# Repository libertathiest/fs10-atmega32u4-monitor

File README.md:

# FS10 Standalone Monitor (ATmega32U4)

A standalone USB monitor and configuration tool for the FCI FS10 Flow Switch, built around the **ATmega32U4** on an Arduino Leonardo–compatible board. It talks to the FS10 over a UART passthrough and shows flow switch condition both graphically and as text on an onboard TFT display — an independent, personal-project replacement for the legacy (uncertified) FCI power accessory.

This was designed, laid out, and manufactured end-to-end: schematic capture and PCB layout in KiCad, enclosure design in FreeCAD, and production through JLCPCB. Physical units are built and in active use.

## Hardware

- **MCU:** ATmega32U4 (Arduino Leonardo form factor, 68.6×53.4mm outline)
- **Display:** 2.4" 240×320 SPI TFT, ILI9341 driver (Adafruit_GFX + Adafruit_ILI9341)
- **Power:** UART passthrough with power arbitration between USB and an external 24V supply; ships with a UL/ETL/CE/FCC-certified wall adapter
- **Enclosure:** Hammond 1593-series compatible, modeled in FreeCAD (STL + parametric source included)
- **PCB:** Designed in KiCad (originally imported from EasyEDA Pro); manufactured and assembled via JLCPCB

## Repo layout

```
firmware/   Arduino sketch (.ino) — display driver, UART passthrough, UI
hardware/   KiCad project (schematic/PCB), FreeCAD enclosure, JLCPCB gerbers + BOM
Assets/     Schematic PDF, design docs, product flyer, front label preview
notes/      Supporting reference material
```

## Status

Completed. Units are built, deployed, and in day-to-day field use.

---
*This is an independently developed project, not an official FCI-branded product.*

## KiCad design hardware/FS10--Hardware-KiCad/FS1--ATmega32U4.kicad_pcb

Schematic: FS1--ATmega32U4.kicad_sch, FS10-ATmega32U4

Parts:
BZ1: Buzzer_5V; MagneticBuzzer_ProSignal_ABT-410-RC; Mfg Part # ABT-410-RC; JLCPCB C252917
C1, C2, C11: 100nF; C_0603_1608Metric; Manufacturer Part CC0603KRX7R9BB104; JLCPCB C14663
C4: 10uF 50V; C_1210_3225Metric; Manufacturer Part CC1210KKX7R9BB106; JLCPCB C596319
C8, C9, C16, C21: 100nF; C_0603_1608Metric; Manufacturer Part CC0603KRX7R9BB104; Digikey_ref 399-C0603C104J4RAC7867CT-ND
C10, C25, C26: 22uF; C_1206; Voltage Rated 10V; Tolerance ±10%; Part CL31A226KPHNNNE; LCSC C5672
C13, C19: 1uF; C_0603_1608Metric; Manufacturer Part CL10A105KB8NNNC; Digikey_ref 399-C0603C105K4RAC7411CT-ND
C14, C15, C17, C18: 1uF; C_0603_1608Metric; Manufacturer Part CL10A105KB8NNNC; JLCPCB C15849
C20: 10u; CP_EIA-3528-21_Kemet-B; Manufacturer Part CA45A-B-20V-10UF-K; Digikey_ref 399-3708-1-ND
C22, C23: 22pF; C_0603; Voltage Rated 50V; Tolerance ±5%; Part CL10C220JB8NNNC; LCSC C1653
C24: 100pF; C_0603; Voltage Rated 50V; Tolerance ±5%; Part CL10C101JB8NNNC; LCSC C14858
CN1: M12_8POS_PIGTAIL_TERMINATION; SIP-9_P2.54mm_Oval; not fitted
D1: SS34B; D_SMB; Manufacturer Part SS34B; LCSC Part Name 3A 40V SMB Schottky diode for buck 5V i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
D2: SMBJ28A-TR; D_SMB; Manufacturer Part SMBJ28A-TR; LCSC Part Name 28V standoff, 45.4V clamp, 600W unidire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
D3: 1N4148W-TP; D_SOD-123; Manufacturer Part 1N4148W-TP; Digikey_ref 1N4148WTPMSCT-ND
D4: SP0503BAHTG; SOT-143; Manufacturer Part SP0503BAHTG; JLCPCB C3040626
D5: US1A; D_SMA; Forward Voltage (Vf@If) 1V@1A; Reverse Voltage (Vr) 50V; Manufacturer Part US1A; LCSC Part Name 1V@1A 50ns Independent Type 1A 50V SMA(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
D6: SS14; D_SMA; Manufacturer Part SS14; LCSC Part Name USB VBUS Schottky isolation into +5V sy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
F1: MF-MSMF050-2; Fuse_1812_4532Metric; Manufacturer Part MF-MSMF050-2; LCSC Part Name 500mA 15V 1812 resettable PTC fuse
H1, H2, H3, H4: M3_SELF_TAP_HOLE; MountingHole_3.2mm_M3
IC2: AP63200WU-7; TSOT-23-6; Manufacturer Part AP63200WU-7; LCSC Part Name 3.8V-32V input, adjustable 2A synchrono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
ICSP1: ICSP; PinHeader_2x03_P2.54mm_Vertical; Digikey_ref A128860-ND; not fitted
J1: DC005; BarrelJack_GCT_DCJ200-10-A_Horizontal; Manufacturer Part DC005; LCSC Part Name DC barrel jack, switched, through-hole,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
J11: Encoder module; PinHeader_1x05_P2.54mm_Vertical
J12: ILI9341 Display; PinHeader_1x10_P2.54mm_Vertical
J13: OLED_I2C_OPTION; PinHeader_1x04_P2.54mm_Vertical; not fitted
L1: 10uH; L_Sunlord_SWPA5040S; Manufacturer Part CKCS5040-10uH/M; JLCPCB C354610
L2: MH2029-300Y; L_0805_2012Metric; Manufacturer Part MH2029-300Y; Digikey_ref MH2029-300YCT-ND
LED1: Wurth_WL-SFTW; LED_RGB_Wuerth-PLCC4_3.2x2.8mm_150141M173100
LED2: 5mm led hand-soldered; LED_D5.0mm-4_RGB
Q_BZ1: 2N7002; SOT-23; LCSC Part Name Low-side MOSFET driver for 5V magnetic 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
R1, R14, R15: 1kΩ; R_0603; Overload Voltage (Max) 75V; Tolerance ±1%; Manufacturer Part 0603WAF1001T5E; LCSC Part Name 100mW Thick Film Resistors 75V ±100ppm/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
R2: 100K; R_0603_1608Metric; Manufacturer Part 0603WAF1003T5E; LCSC Part Name Resistance:100kΩ Package:0603 ±1% 100mW
R3, R4: 1M; R_0603_1608Metric; Manufacturer Part 0603WAF1004T5E; LCSC Part Name Resistance:1MΩ Package:0603 ±1% 100mW
R5, R6: 22; R_0603_1608Metric; Manufacturer Part 0603WAF220JT5E; LCSC Part Name Resistance:22Ω Package:0603 ±1% 100mW
R7: 150k; R_0603_1608Metric; Manufacturer Part 0603WAF1503T5E; LCSC Part Name Resistance:150kΩ Package:0603 ±1% 100mW
R8: 22k; R_0603_1608Metric; Manufacturer Part 0603WAF2202T5E; LCSC Part Name Resistance:22kΩ Package:0603 ±1% 100mW
R9: 169K; R_0603_1608Metric; Manufacturer Part 0603WAF1693T5E; LCSC Part Name Resistance:169kΩ Package:0603 ±1% 100mW
R10: 30K; R_0603_1608Metric; Manufacturer Part 0603WAF3002T5E; LCSC Part Name Resistance:30kΩ Package:0603 ±1% 100mW
R21: 270Ω; R_0805; Overload Voltage (Max) 150V; Tolerance ±1%; Manufacturer Part 0805W8F2700T5E; LCSC Part Name 125mW Thick Film Resistors 150V ±100ppm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
RESET1: SKHHLUA010; SW_Tactile_SKHH_Angled; Manufacturer Part SKHHLUA010; LCSC C139764
R_BZ1: 1k; R_0805_2012Metric; Manufacturer Part 0805W8F1001T5E; LCSC Part Name Resistance:1kΩ Package:0805 ±1% 125mW
R_BZ2: 100k; R_0805_2012Metric; Manufacturer Part 0805W8F1003T5E; LCSC Part Name Resistance:100kΩ Package:0805 ±1% 125mW
SW1: HX KCD11-BL; SW-TH_KCD11-BL; Manufacturer Part HX KCD11-BL; JLCPCB C6917329
SW2: K2-1102SP-A4SC-04; Push_Hybrid_SMD_THR_12x12mm; Manufacturer Part K2-1102SP-A4SC-04; LCSC Part Name 12x12mm SMD-4P SPST tactile switch, 7.5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
TP1, TP2: Pin_D0.9mm_L10.0mm_W2.4mm_FlatFork
TP4, TP5, TP6, TP7: TP; SolderWire-0.1sqmm_1x01_D0.4mm_OD1mm
U2: ATMEGA32U4-XUAU; TQFP-44_10x10mm_P0.8mm; Manufacturer Part ATMEGA32U4-AU; JLCPCB C44854
U3: MAX232EIDR; SOIC-16_3.9x9.9mm_P1.27mm; Manufacturer Part MAX232EIDR; JLCPCB C273639
USB1: USB-109C-B-CU; USB-B-TH_USB-109C-B-CU; Manufacturer Part USB-109C-B-CU; JLCPCB C20611692
X1: X322516MLB4SI; OSC-SMD_4P-L3.2-W2.5-BL; Frequency Tolerance ±10ppm; Manufacturer Part X322516MLB4SI; LCSC Part Name 16MHz Surface Mount Crystal 9pF ±10ppm 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

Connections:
24V: C1.1, C4.1 (+), CN1.1 (WTE), IC2.2 (EN), IC2.3 (VIN), R7.1, SW1.2
+4-20: CN1.3 (GRN), TP1.1 (1_1)
+5V: C11.2, D1.1 (C), D6.1 (C), ICSP1.2, J11.2, J12.1 (+5V), J12.8 (LED+), J12.10 (TFT_BL), J13.2, L2.2, LED1.1 (A), LED2.2 (A), R21.1, U2.2 (UVCC), U2.14 (VCC), U2.34 (VCC1), U3.16 (VCC)
/24Vraw: D2.1 (C), J1.1, SW1.1
/AREF: C13.2, C16.2, U2.42 (AREF)
/AVCC: C8.1, C9.1, D3.1 (C), L2.1, U2.24 (AVCC), U2.44 (AVCC1)
/BLU: CN1.7 (BLU), U3.14 (DOUT1)
/BUCK_RAW: C10.1, C24.1, C25.1, C26.1, D1.2 (A), L1.2, R9.2
/BUZZER_CTRL: R_BZ1.1, U2.29 ((PCINT5/OC1A/#OC4B/ADC12)PB5)
/ENC_A_D4: J11.5, U2.25 ((ICP1/ADC8)PD4)
/ENC_B_D5: J11.4, U2.22 ((XCK1/#CTS)PD5)
/ENC_SW_D6: J11.3, U2.26 ((T1/#OC4D/ADC9)PD6)
/FB_DIV: C24.2, IC2.1 (FB), R9.1, R10.2
/GPIO_PB6: TP4.1 (Pin_1_1), U2.30 ((PCINT6/OC1B/OC4B/ADC13)PB6)
/GPIO_PB7: R7.2, R8.2, U2.12 ((PCINT7/OC0A/OC1C/#RTS)PB7)
/GPIO_PE2: TP6.1 (Pin_1_1), U2.33 ((#HWB)PE2)
/GPIO_PE6: TP5.1 (Pin_1_1), U2.1 ((INT6/AIN0)PE6)
/GPIO_PF7: TP7.1 (Pin_1_1), U2.36 ((ADC7/TDI)PF7)
/LED_BLU: R1.2, U2.37 ((ADC6/TDO)PF6)
/LED_GRN: R14.2, U2.38 ((ADC5/TMS)PF5)
/LED_RED: R15.2, U2.39 ((ADC4/TCK)PF4)
/MISO: ICSP1.1, J12.9 (MISO), U2.11 ((PD0/MISO/PCINT3)PB3)
/MOSI: ICSP1.4, J12.6 (MOSI), U2.10 ((PDI/MOSI/PCINT2)PB2)
/NC: CN1.4 (YEL), U2.40 ((ADC1)PF1)
/NO: CN1.6 (PNK), U2.41 ((ADC0)PF0)
/PANEL_SW_D7: SW2.1, U2.27 ((T0/OC4D/ADC10)PD7)
/RED: CN1.8 (RED), U3.13 (RIN1)
/RESET: D3.2 (A), ICSP1.5, J12.4 (RESET), RESET1.1, U2.13 (RESET)
/SCK: ICSP1.3, J12.7 (SCK), U2.9 ((SCLK/PCINT1)PB1)
/SCL: J13.3, U2.18 ((OC0B/SCL/INT0)PD0)
/SDA: J13.4, U2.19 ((SDA/INT1)PD1)
/TFT_CS: J12.3 (TFT_CS), U2.8 ((SS/PCINT0)PB0)
/TFT_DC: J12.5 (TFT_DC), U2.31 ((OC3A/#0C4A)PC6)
/UART_RXD1: U2.20 ((RXD1/AIN1/INT2)PD2), U3.12 (ROUT1)
/UART_TXD1: U2.21 ((TXD1/INT3)PD3), U3.11 (DIN1)
/UCAP: C19.2, U2.6 (UCAP)
/USB_CONN+: D4.2, R6.1, USB1.3 (D+)
/USB_CONN-: D4.3, R5.1, USB1.2 (D-)
/USB_DEV+: R6.2, U2.4 (D+)
/USB_DEV-: R5.2, U2.3 (D-)
/USB_PRESENT: R2.2, R3.2, U2.28 ((ADC11/PCINT4)PB4)
/XTAL101: C23.2, R4.1, U2.17 (XTAL1), X1.1 (OSC)
/XTAL102: C22.2, R4.2, U2.16 (XTAL2), X1.3 (OSC)
GND: C1.2, C4.2 (-), C8.2, C9.2, C10.2, C11.1, C13.1, C14.1, C16.1, C17.1, C19.1, C20.2 (-), C21.1, C22.1, C23.1, C25.2, C26.2, CN1.2 (BRN), CN1.5 (GRY), CN1.9, D2.2 (A), D4.1, IC2.4 (GND), ICSP1.6, J1.2, J11.1, J12.2 (GND), J13.1, Q_BZ1.2 (S), R3.1, R8.1, R10.1, RESET1.2, R_BZ2.2, SW2.2, TP2.1 (1_1), U2.5 (UGND), U2.15 (GND), U2.23 (GND1), U2.35 (GND2), U2.43 (GND3), U3.15 (GND), USB1.4 (GND), USB1.5 (GND), USB1.6 (GND), X1.2 (GND), X1.4 (GND)
unnamed: BZ1.1 (+), D5.1, R21.2
unnamed: BZ1.2 (-), D5.2, Q_BZ1.3 (D)
unnamed: C2.2, IC2.6 (BST)
unnamed: C2.1, IC2.5 (SW), L1.1
unnamed: LED1.2 (B), LED2.4 (B), R1.1
unnamed: LED1.4 (G), LED2.3 (G), R14.1
unnamed: LED1.3 (R), LED2.1 (R), R15.1
unnamed: Q_BZ1.1 (G), R_BZ1.2, R_BZ2.1
unnamed: C15.2, U3.1 (C1+)
unnamed: C15.1, U3.3 (C1−)
unnamed: C18.1, U3.4 (C2+)
unnamed: C18.2, U3.5 (C2−)
unnamed: C14.2, U3.2 (VS+)
unnamed: C17.2, U3.6 (VS−)
unnamed: D4.4, F1.2, USB1.1 (VBUS)
VUSB: C20.1 (+), C21.2, D6.2 (A), F1.1, R2.1, U2.7 (VBUS)

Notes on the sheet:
D4 isolates BUCK_5V from USB-powered +5V rail
AP63200 adjustable buck: L=10uH, CIN=10uF 50V + 100nF, COUT=2x22uF, CBST=100nF, Cff=100pF
USB VBUS -> D6 Schottky -> +5V; buck D1 wins when 24V is present
4-20 side connections
+5V_SYS SOURCE ORING

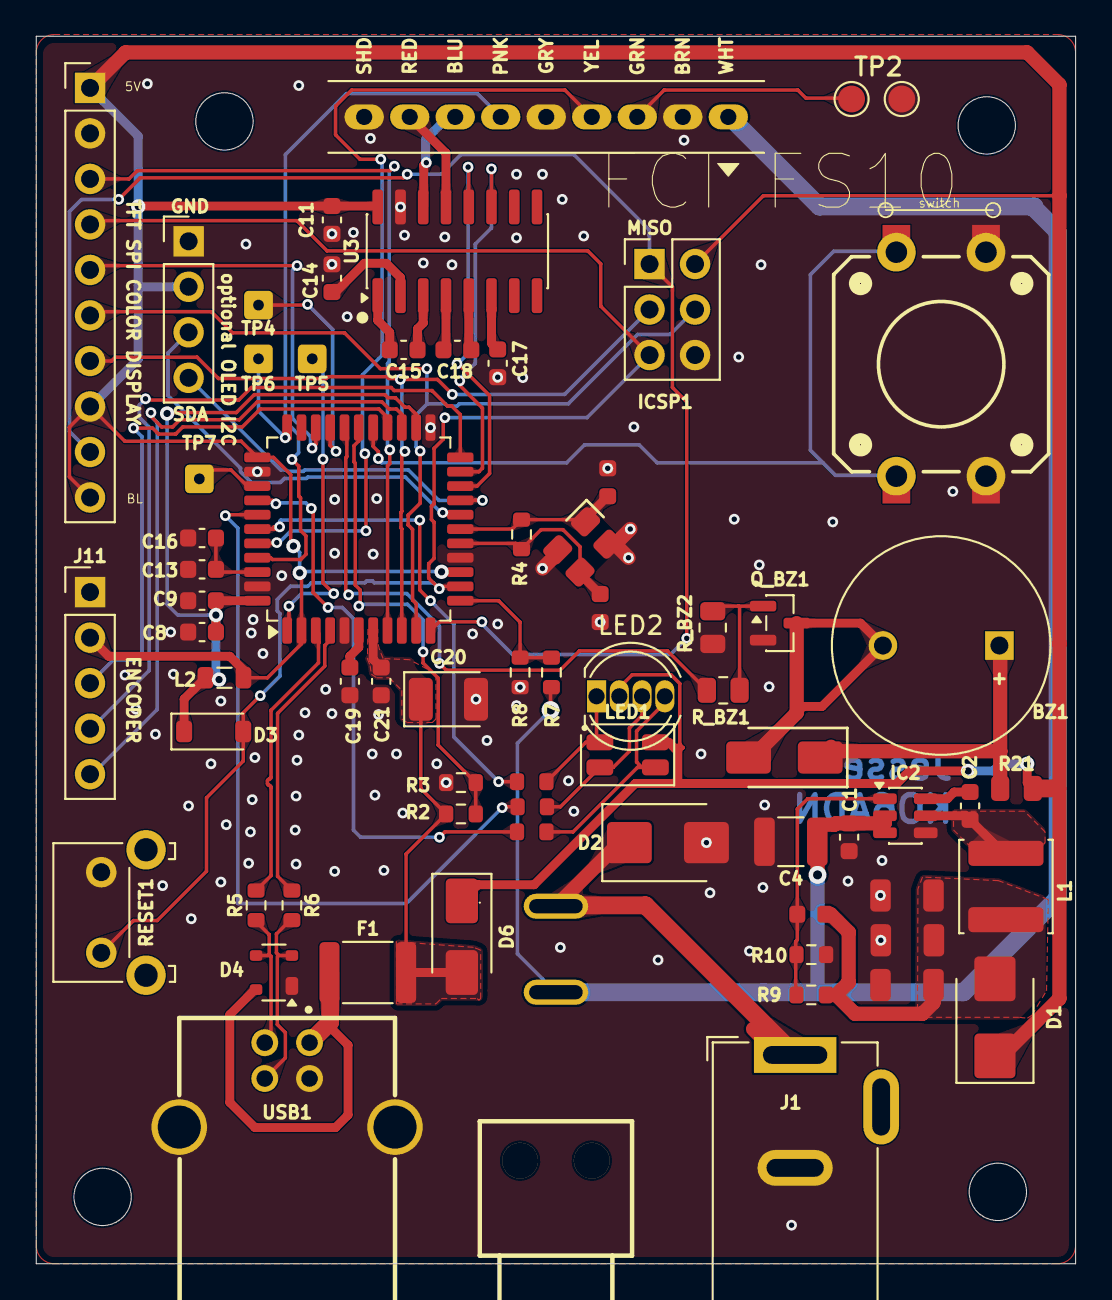
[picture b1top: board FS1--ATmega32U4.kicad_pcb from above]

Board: 2 copper layers, 58.0 x 68.5 mm, 73 parts (0 on the bottom side), 60 nets.

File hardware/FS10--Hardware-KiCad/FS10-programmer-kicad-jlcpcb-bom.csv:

"Designator","Comment","Footprint","LCSC Part #","JLCPCB","Supplier Part","Manufacturer Part","Manufacturer","Description","Quantity","DNP"
"BZ1","Buzzer_5V","Buzzer_Beeper:MagneticBuzzer_ProSignal_ABT-410-RC","C252917","C252917","","","","","1",""
"C1,C2,C8,C9,C11,C16,C21","100nF","Capacitor_SMD:C_0603_1608Metric","C14663","C14663","C14663","CC0603KRX7R9BB104","YAGEO","100nF 50V X7R 0603 MLCC","7",""
"C4","10uF 50V","Capacitor_SMD:C_1210_3225Metric","C596319","C596319","C596319","CC1210KKX7R9BB106","YAGEO","10uF 50V X7R 1210 MLCC","1",""
"C10,C25,C26","22uF","PCM_JLCPCB:C_1206","C5672","C5672","C5672","CL31A226KPHNNNE","Samsung Electro-Mechanics","10V 22uF X5R ±10% 1206 Multilayer Ceramic Capacitors MLCC - SMD/SMT ROHS","3",""
"C13-C15,C17-C19","1uF","Capacitor_SMD:C_0603_1608Metric","C15849","C15849","C15849","CL10A105KB8NNNC","Samsung Electro-Mechanics","1uF 50V X5R 0603 MLCC","6",""
"C20","10u","Capacitor_Tantalum_SMD:CP_EIA-3528-21_Kemet-B","C2976904","C2976904","C2976904","CA45A-B-20V-10UF-K","CEC(Shenzhen Zhenhua XinYun Elec)","10uF 20V Case-B 3528 tantalum capacitor","1",""
"C22,C23","22pF","PCM_JLCPCB:C_0603","C1653","C1653","C1653","CL10C220JB8NNNC","Samsung Electro-Mechanics","50V 22pF C0G ±5% 0603 Multilayer Ceramic Capacitors MLCC - SMD/SMT ROHS","2",""
"C24","100pF","PCM_JLCPCB:C_0603","C14858","C14858","C14858","CL10C101JB8NNNC","Samsung Electro-Mechanics","100pF 50V C0G ±5% 0603 Multilayer Ceramic Capacitors MLCC - SMD/SMT ROHS","1",""
"CN1","M12_8POS_PIGTAIL_TERMINATION","FS10-programmer-local:SIP-9_P2.54mm_Oval","","","","","","","1","DNP"
"D1","SS34B","Diode_SMD:D_SMB","C13762","C13762","C13762","SS34B","MDD","3A 40V SMB Schottky diode for buck 5V isolation into +5V system rail","1",""
"D2","SMBJ28A-TR","Diode_SMD:D_SMB","C96335","C96335","C96335","SMBJ28A-TR","STMicroelectronics","28V standoff, 45.4V clamp, 600W unidirectional SMB TVS for 24V raw input","1",""
"D3","1N4148W-TP","Diode_SMD:D_SOD-123","","","","1N4148W-TP","MCC","","1",""
"D4","SP0503BAHTG","Package_TO_SOT_SMD:SOT-143","C3040626","C3040626","C3040626","SP0503BAHTG","TECH PUBLIC(台舟)","Polarity:Unidirectional Reverse Stand-Off Voltage (Vrwm):5.5V Clamping Voltage:14V Peak Pulse Current (Ipp):10A@8/20us Peak Pulse Power Dissipation (Ppp):150W@8/20us Voltage - Breakdown:6V Reverse Leakage Current (Ir):80nA Number of Channels:three routes","1",""
"D5","US1A","PCM_JLCPCB:D_SMA","C18199125","C18199125","C18199125","US1A","hongjiacheng","1V@1A 50ns Independent Type 1A 50V SMA(DO-214AC) Fast Recovery / High Efficiency Diodes ROHS","1",""
"D6","SS14","Diode_SMD:D_SMA","","","","SS14","","USB VBUS Schottky isolation into +5V system rail","1",""
"F1","MF-MSMF050-2","Fuse:Fuse_1812_4532Metric","C17313","C17313","C17313","MF-MSMF050-2","BOURNS","500mA 15V 1812 resettable PTC fuse","1",""
"IC2","AP63200WU-7","Package_TO_SOT_SMD:TSOT-23-6","C2071868","C2071868","C2071868","AP63200WU-7","Diodes Incorporated","3.8V-32V input, adjustable 2A synchronous buck converter; feedback divider set above 5V to compensate D1 drop","1",""
"ICSP1","ICSP","Connector_PinHeader_2.54mm:PinHeader_2x03_P2.54mm_Vertical","","","","","TE","","1","DNP"
"J1","DC005","Connector_BarrelJack:BarrelJack_GCT_DCJ200-10-A_Horizontal","C5280493","C5280493","C5280493","DC005","","DC barrel jack, switched, through-hole, hand/deselect assembly as needed","1",""
"J11","Encoder module","Connector_PinHeader_2.54mm:PinHeader_1x05_P2.54mm_Vertical","","","","","","","1",""
"J12","ILI9341 Display","Connector_PinHeader_2.54mm:PinHeader_1x10_P2.54mm_Vertical","","","","","","","1",""
"J13","OLED_I2C_OPTION","Connector_PinHeader_2.54mm:PinHeader_1x04_P2.54mm_Vertical","","","","","","","1","Optional"
"L1","10uH","Inductor_SMD:L_Sunlord_SWPA5040S","C354610","C354610","C354610","CKCS5040-10uH/M","CENKER","AP63200 buck inductor, shielded 10uH with saturation current above 2.5A","1",""
"L2","MH2029-300Y","Inductor_SMD:L_0805_2012Metric","","","","MH2029-300Y","Bourns","","1",""
"LED1","Wurth_WL-SFTW","PCM_LED_SMD_AKL:LED_RGB_Wuerth-PLCC4_3.2x2.8mm_150141M173100","","","","","","","1",""
"LED2","5mm led hand-soldered","LED_THT:LED_D5.0mm-4_RGB","","","","","","","1",""
"Q_BZ1","2N7002","Package_TO_SOT_SMD:SOT-23","C28646312","C28646312","C28646312","","","Low-side MOSFET driver for 5V magnetic buzzer","1",""
"R1,R14,R15","1kΩ","PCM_JLCPCB:R_0603","C21190","C21190","C21190","0603WAF1001T5E","UNI-ROYAL(Uniroyal Elec)","100mW Thick Film Resistors 75V ±100ppm/°C ±1% 1kΩ 0603 Chip Resistor - Surface Mount ROHS","3",""
"R2","100K","Resistor_SMD:R_0603_1608Metric","C25803","C25803","C25803","0603WAF1003T5E","UNI-ROYAL(Uniroyal Elec)","Resistance:100kΩ Package:0603 ±1% 100mW","1",""
"R3,R4","1M","Resistor_SMD:R_0603_1608Metric","C22935","C22935","C22935","0603WAF1004T5E","UNI-ROYAL(Uniroyal Elec)","Resistance:1MΩ Package:0603 ±1% 100mW","2",""
"R5,R6","22","Resistor_SMD:R_0603_1608Metric","C23345","C23345","C23345","0603WAF220JT5E","UNI-ROYAL(Uniroyal Elec)","Resistance:22Ω Package:0603 ±1% 100mW","2",""
"R7","150k","Resistor_SMD:R_0603_1608Metric","C22807","C22807","C22807","0603WAF1503T5E","UNI-ROYAL(Uniroyal Elec)","Resistance:150kΩ Package:0603 ±1% 100mW","1",""
"R8","22k","Resistor_SMD:R_0603_1608Metric","C31850","C31850","C31850","0603WAF2202T5E","UNI-ROYAL(Uniroyal Elec)","Resistance:22kΩ Package:0603 ±1% 100mW","1",""
"R9","169K","Resistor_SMD:R_0603_1608Metric","C22817","C22817","C22817","0603WAF1693T5E","UNI-ROYAL(Uniroyal Elec)","Resistance:169kΩ Package:0603 ±1% 100mW","1",""
"R10","30K","Resistor_SMD:R_0603_1608Metric","C22984","C22984","C22984","0603WAF3002T5E","UNI-ROYAL(Uniroyal Elec)","Resistance:30kΩ Package:0603 ±1% 100mW","1",""
"R21","270Ω","PCM_JLCPCB:R_0805","C17590","C17590","C17590","0805W8F2700T5E","UNI-ROYAL(Uniroyal Elec)","125mW Thick Film Resistors 150V ±100ppm/°C ±1% 270Ω 0805 Chip Resistor - Surface Mount ROHS","1",""
"RESET1","SKHHLUA010","Button_Switch_THT:SW_Tactile_SKHH_Angled","C139764","C139764","C139764","SKHHLUA010","ALPSALPINE","Tactile Switch SPST-NO side actuated through-hole right angle, 6.2x6.2mm, 5.85mm stem, wave soldering","1",""
"R_BZ1","1k","Resistor_SMD:R_0805_2012Metric","C17513","C17513","C17513","0805W8F1001T5E","UNI-ROYAL(Uniroyal Elec)","Resistance:1kΩ Package:0805 ±1% 125mW","1",""
"R_BZ2","100k","Resistor_SMD:R_0805_2012Metric","C149504","C149504","C149504","0805W8F1003T5E","UNI-ROYAL(Uniroyal Elec)","Resistance:100kΩ Package:0805 ±1% 125mW","1",""
"SW1","HX KCD11-BL","easyedatokicad:SW-TH_KCD11-BL","C6917329","C6917329","C6917329","HX KCD11-BL","hanxia","SPST rocker switch, through-hole, hand/deselect assembly as needed","1",""
"SW2","K2-1102SP-A4SC-04","FS10-programmer:Push_Hybrid_SMD_THR_12x12mm","C83214","C83214","C83214","K2-1102SP-A4SC-04","Korean Hroparts Elec","12x12mm SMD-4P SPST tactile switch, 7.5mm height","1",""
"TP1,TP2","","Connector_Pin:Pin_D0.9mm_L10.0mm_W2.4mm_FlatFork","","","","","","","2",""
"TP5-TP7","TP","Connector_Wire:SolderWire-0.1sqmm_1x01_D0.4mm_OD1mm","","","","","","","3",""
"U2","ATMEGA32U4-XUAU","Package_QFP:TQFP-44_10x10mm_P0.8mm","C44854","C44854","C44854","ATMEGA32U4-AU","Microchip","","1",""
"U3","MAX232EIDR","Package_SO:SOIC-16_3.9x9.9mm_P1.27mm","C273639","C273639","C273639","MAX232EIDR","TI(德州仪器)","Type:transceiver Number of Drivers:2 Number of Receivers:2 Data Rate:250Kbps Data Rate:250Kbps Voltage - Supply:4.5V~5.5V Voltage - Supply:4.5V~5.5V charge pump:Yes Operating Temperature:-40°C~+85°C Operating Temperature:-40°C~+85°C","1",""
"USB1","USB-109C-B-CU","easyedatokicad:USB-B-TH_USB-109C-B-CU","C20611692","C20611692","C20611692","USB-109C-B-CU","HOOYA","USB Type-B right-angle through-hole connector","1",""
"X1","X322516MLB4SI","PCM_JLCPCB:OSC-SMD_4P-L3.2-W2.5-BL","C13738","C13738","C13738","X322516MLB4SI","Yangxing Tech","16MHz Surface Mount Crystal 9pF ±10ppm ±20ppm SMD3225-4P Crystals ROHS","1",""

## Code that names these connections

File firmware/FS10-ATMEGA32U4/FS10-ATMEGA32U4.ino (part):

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#include <string.h>

constexpr uint32_t FS10_BAUD = 9600;
constexpr uint8_t TFT_CS = 17;    // PB0, J12-3
constexpr uint8_t TFT_DC = 5;     // PC6, J12-5
constexpr int8_t TFT_RST = -1;    // J12 reset is board reset
constexpr uint8_t BUZZER_PIN = 9; // PB5, BUZZER_CTRL
constexpr uint8_t TFT_BL_PIN = 10; // PB6 / GPIO_PB6, hardware PWM backlight
constexpr uint8_t LED_RED_PIN = A3; // PF4, common-anode RGB LED cathode
constexpr uint8_t LED_GRN_PIN = A2; // PF5, common-anode RGB LED cathode
constexpr uint8_t LED_BLU_PIN = A1; // PF6, common-anode RGB LED cathode
constexpr uint8_t RELAY_HI_BIT = 1; // PF1, NC relay contact sense
constexpr uint8_t RELAY_LO_BIT = 0; // PF0, NO relay contact sense
constexpr uint8_t SUPPLY_24V_BIT = 7; // PB7, 24V-present sense
constexpr uint8_t LINE_MAX = 64;
constexpr uint8_t BRIDGE_CHUNK_MAX = 32;
constexpr uint16_t DISPLAY_TICK_MS = 500;
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static long relayLimit10 = LONG_MIN;

static void initUsbPresentSense() {
  DDRB &= ~_BV(4);  // PB4 / USB_PRESENT input
  PORTB &= ~_BV(4); // External VUSB divider drives this line.
}

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}

static void setRgbLed(bool red, bool green, bool blue) {
  digitalWrite(LED_RED_PIN, red ? LOW : HIGH);
  digitalWrite(LED_GRN_PIN, green ? LOW : HIGH);
  digitalWrite(LED_BLU_PIN, blue ? LOW : HIGH);
}

static void flashRgbLed(bool red, bool green, bool blue, uint16_t ms) {
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
static int8_t getSwitchStatus() {
  uint8_t relayPins = PINF;
  uint8_t pf1 = (relayPins & _BV(1)) != 0;
  uint8_t pf0 = (relayPins & _BV(0)) != 0;
  uint8_t raw = (pf1 << 1) | pf0;
  if (raw == 1) return 0;
  if (raw == 2) return 1;
  return -1;
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  initUsbPresentSense();
  initSupplySense();
  initRelaySense();
  pinMode(LED_RED_PIN, OUTPUT);
  pinMode(LED_GRN_PIN, OUTPUT);
  pinMode(LED_BLU_PIN, OUTPUT);
  pinMode(BUZZER_PIN, OUTPUT);
  digitalWrite(BUZZER_PIN, LOW);
  setTftBacklight();
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
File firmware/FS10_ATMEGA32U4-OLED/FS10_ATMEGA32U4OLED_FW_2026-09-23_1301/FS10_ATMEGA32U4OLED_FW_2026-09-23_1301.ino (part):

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
constexpr uint32_t FS10_BAUD = 9600;
constexpr bool DEMO_MODE = false;  // Set to false for production
// J13 optional OLED header: pin 3 is PD1/SDA, pin 4 is PD0/SCL.
constexpr uint8_t OLED_I2C_ADDRESS = 0x3C;
constexpr uint8_t OLED_WIDTH = 128;
constexpr uint8_t OLED_HEIGHT = 64;
constexpr int8_t OLED_RESET = -1;
constexpr uint8_t BUZZER_PIN = 9; // PB5, BUZZER_CTRL
constexpr uint8_t LED_RED_PIN = A3; // PF4, common-anode RGB LED cathode
constexpr uint8_t LED_GRN_PIN = A2; // PF5, common-anode RGB LED cathode
constexpr uint8_t LED_BLU_PIN = A1; // PF6, common-anode RGB LED cathode
constexpr uint8_t PANEL_BUTTON_BIT = 7; // PD7, PANEL_SW_D7 on custom board
constexpr uint8_t RELAY_HI_BIT = 1; // PF1, NC relay contact sense
constexpr uint8_t RELAY_LO_BIT = 0; // PF0, NO relay contact sense
constexpr uint8_t SUPPLY_24V_BIT = 7; // PB7, 24V-present sense
constexpr uint8_t LINE_MAX = 64;
constexpr uint8_t BRIDGE_CHUNK_MAX = 32;
constexpr uint16_t DISPLAY_TICK_MS = 500;
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static long relayLimit10 = LONG_MIN;

static void initUsbPresentSense() {
  DDRB &= ~_BV(4);  // PB4 / USB_PRESENT input
  PORTB &= ~_BV(4); // External VUSB divider drives this line.
}

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}

static void setRgbLed(bool red, bool green, bool blue) {
  digitalWrite(LED_RED_PIN, red ? LOW : HIGH);
  digitalWrite(LED_GRN_PIN, green ? LOW : HIGH);
  digitalWrite(LED_BLU_PIN, blue ? LOW : HIGH);
}

static void flashRgbLed(bool red, bool green, bool blue, uint16_t ms) {
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
static int8_t getSwitchStatus() {
  uint8_t relayPins = PINF;
  uint8_t pf1 = (relayPins & _BV(1)) != 0;
  uint8_t pf0 = (relayPins & _BV(0)) != 0;
  uint8_t raw = (pf1 << 1) | pf0;
  if (raw == 1) return 0;
  if (raw == 2) return 1;
  return -1;
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  initUsbPresentSense();
  initSupplySense();
  initRelaySense();
  pinMode(LED_RED_PIN, OUTPUT);
  pinMode(LED_GRN_PIN, OUTPUT);
  pinMode(LED_BLU_PIN, OUTPUT);
  pinMode(BUZZER_PIN, OUTPUT);
  // Configure PANEL_BUTTON_BIT (PD7) as input with pull-up
  DDRD &= ~_BV(PANEL_BUTTON_BIT);   // Set PD7 as input (clear bit)
  PORTD |= _BV(PANEL_BUTTON_BIT);   // Enable internal pull-up
  digitalWrite(BUZZER_PIN, LOW);
  setRgbLed(false, false, false);
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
